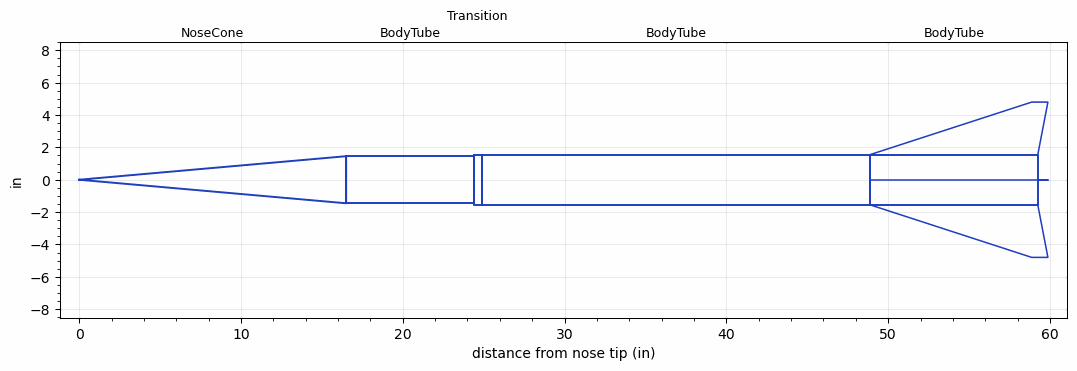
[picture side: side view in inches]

<RASAeroDocument>
 <FileVersion>2</FileVersion>
 <RocketDesign>
  <NoseCone>
   <Length>16.5</Length>
   <Diameter>2.91</Diameter>
   <Shape>Conical</Shape>
   <Location>0</Location>
  </NoseCone>
  <BodyTube>
   <Length>7.874</Length>
   <Diameter>2.91</Diameter>
   <Location>16.5</Location>
  </BodyTube>
  <Transition>
   <Length>0.5</Length>
   <Diameter>3.098</Diameter>
   <RearDiameter>3.098</RearDiameter>
   <Location>24.374</Location>
  </Transition>
  <BodyTube>
   <Length>24</Length>
   <Diameter>3.098</Diameter>
   <Location>24.874</Location>
  </BodyTube>
  <BodyTube>
   <Length>10.375</Length>
   <Diameter>3.098</Diameter>
   <Location>48.8739</Location>
   <Fin>
    <Count>4</Count>
    <Chord>10.375</Chord>
    <Span>3.25</Span>
    <SweepDistance>10</SweepDistance>
    <TipChord>1</TipChord>
    <Thickness>0.2</Thickness>
    <Location>10.375</Location>
    <AirfoilSection>Subsonic NACA</AirfoilSection>
   </Fin>
  </BodyTube>
  <Surface>Rough Camouflage Paint</Surface>
  <CD>0</CD>
  <ModifiedBarrowman>False</ModifiedBarrowman>
  <Turbulence>False</Turbulence>
  <UseBooster1>False</UseBooster1>
  <UseBooster2>False</UseBooster2>
 </RocketDesign>
 <LaunchSite>
  <Altitude>0</Altitude>
  <Pressure>29.9214</Pressure>
  <RodAngle>5</RodAngle>
  <RodLength>10</RodLength>
  <Temperature>59</Temperature>
  <WindSpeed>4.4739</WindSpeed>
 </LaunchSite>
 <Recovery>
  <Altitude1>0</Altitude1>
  <Altitude2>0</Altitude2>
  <DeviceType1>None</DeviceType1>
  <DeviceType2>None</DeviceType2>
  <Event1>False</Event1>
  <Event2>False</Event2>
  <Size1>0</Size1>
  <Size2>0</Size2>
  <EventType1>None</EventType1>
  <EventType2>None</EventType2>
  <CD1>0</CD1>
  <CD2>0</CD2>
 </Recovery>
 <SimulationList>
  <Simulation>
   <SustainerLaunchWt>9.6302</SustainerLaunchWt>
   <SustainerCG>34.7616</SustainerCG>
   <SustainerIgnitionDelay>0</SustainerIgnitionDelay>
   <Booster1SeparationDelay>0</Booster1SeparationDelay>
   <Booster1IgnitionDelay>0</Booster1IgnitionDelay>
   <IncludeBooster1>False</IncludeBooster1>
   <Booster2Delay>0</Booster2Delay>
   <IncludeBooster2>False</IncludeBooster2>
  </Simulation>
  <Simulation>
   <SustainerLaunchWt>6.8017</SustainerLaunchWt>
   <SustainerCG>27.3367</SustainerCG>
   <SustainerIgnitionDelay>0</SustainerIgnitionDelay>
   <Booster1SeparationDelay>0</Booster1SeparationDelay>
   <Booster1IgnitionDelay>0</Booster1IgnitionDelay>
   <IncludeBooster1>False</IncludeBooster1>
   <Booster2Delay>0</Booster2Delay>
   <IncludeBooster2>False</IncludeBooster2>
  </Simulation>
  <Simulation>
   <SustainerLaunchWt>6.8017</SustainerLaunchWt>
   <SustainerCG>27.3367</SustainerCG>
   <SustainerIgnitionDelay>0</SustainerIgnitionDelay>
   <Booster1SeparationDelay>0</Booster1SeparationDelay>
   <Booster1IgnitionDelay>0</Booster1IgnitionDelay>
   <IncludeBooster1>False</IncludeBooster1>
   <Booster2Delay>0</Booster2Delay>
   <IncludeBooster2>False</IncludeBooster2>
  </Simulation>
 </SimulationList>
</RASAeroDocument>
